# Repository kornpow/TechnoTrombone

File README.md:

# TechnoTrombone
Trombone Tutor for Raspberry Pi, and using Adafruit Neopixels

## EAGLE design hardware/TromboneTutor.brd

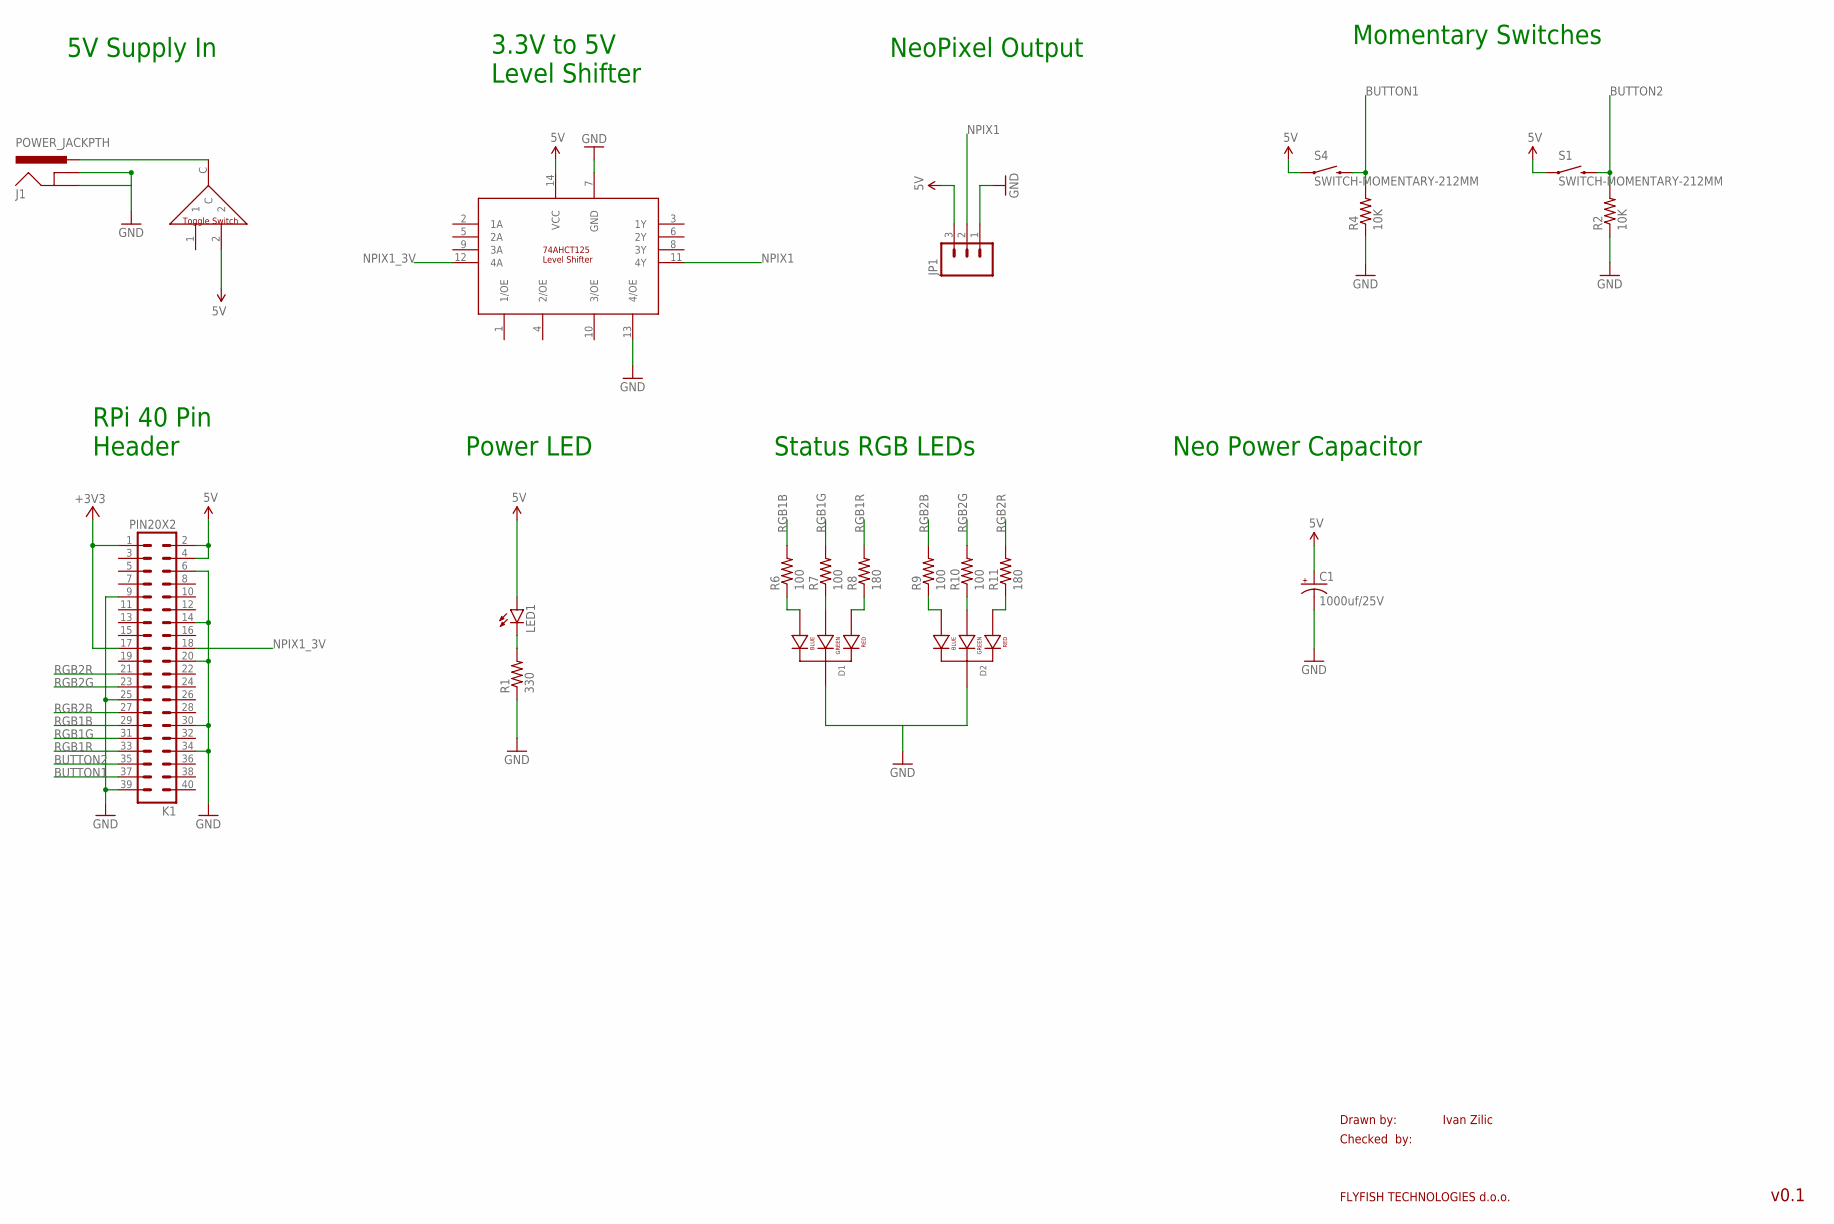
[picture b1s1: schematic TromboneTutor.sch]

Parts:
C1: 1000uf/25V; CPOL-RADIAL-1000UF-25V-KIT
D1, D2: LED-RGB-CC-THRUDIFFUSE; LED-RGB-THRU
J1: POWER_JACKPTH; POWER_JACK_PTH
JP1: M03PTH; 1X03
K1: PIN20X2; PIN_20X2
LED1: LED5MM
R1: 330; AXIAL-0.3
R2, R4: 10K; AXIAL-0.3-KIT
R6, R7, R9, R10: 100; AXIAL-0.3
R8, R11: 180; AXIAL-0.3
S1, S4: SWITCH-MOMENTARY-212MM; TACTILE-PTH-12MM
U$1: 74AHCT125_LEVELSHIFT; DIL14
U$2: TOGGLE_SWITCH_ESTORE

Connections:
5V: C1.+, JP1.3, K1.2, K1.4, LED1.A, S1.1, S4.1, U$1.14 (VCC), U$2.2
+3V3: K1.1, K1.17
BUTTON1: K1.37, R4.P$2 (2), S4.3 (2)
BUTTON2: K1.35, R2.P$2 (2), S1.3 (2)
GND: C1.-, D1.2 (CATHODE), D2.2 (CATHODE), J1.GND, J1.GNDBREAK, JP1.1, K1.6, K1.9, K1.14, K1.20, K1.25, K1.30, K1.34, K1.39, R1.P$1 (1), R2.P$1 (1), R4.P$1 (1), U$1.7 (GND), U$1.13 (4/OE)
unnamed: J1.PWR, U$2.C
unnamed: D1.4 (BLUE_CATHODE), R6.P$1 (1)
unnamed: D1.3 (GREEN_CATHODE), R7.P$1 (1)
unnamed: D1.1 (RED_CATHODE), R8.P$1 (1)
unnamed: D2.4 (BLUE_CATHODE), R9.P$1 (1)
unnamed: LED1.K (C), R1.P$2 (2)
unnamed: D2.3 (GREEN_CATHODE), R10.P$1 (1)
unnamed: D2.1 (RED_CATHODE), R11.P$1 (1)
NPIX1: JP1.2, U$1.11 (4Y)
NPIX1_3V: K1.18, U$1.12 (4A)
RGB1B: K1.29, R6.P$2 (2)
RGB1G: K1.31, R7.P$2 (2)
RGB1R: K1.33, R8.P$2 (2)
RGB2B: K1.27, R9.P$2 (2)
RGB2G: K1.23, R10.P$2 (2)
RGB2R: K1.21, R11.P$2 (2)

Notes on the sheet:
Drawn by:
Checked by:
FLYFISH TECHNOLOGIES d.o.o.
Ivan Zilic
v0.1
NeoPixel Output
3.3V to 5V Level Shifter
RPi 40 Pin Header
5V Supply In
Power LED
Status RGB LEDs
Momentary Switches
Neo Power Capacitor

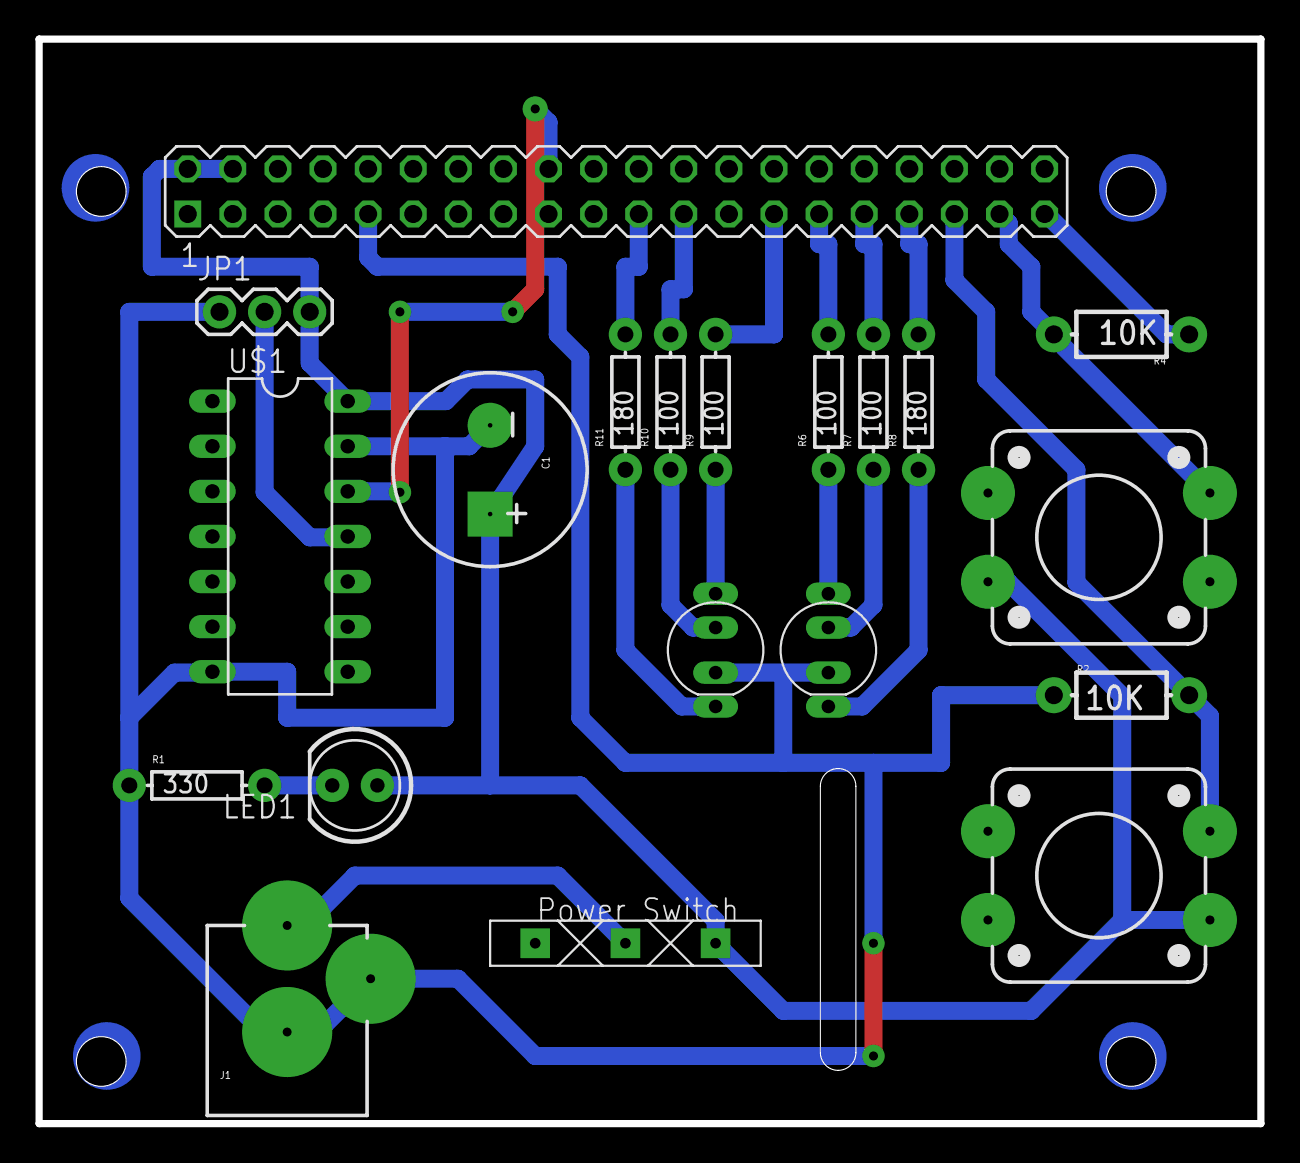
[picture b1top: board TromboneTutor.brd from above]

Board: 2 copper layers, 68.8 x 61.1 mm, 20 parts (0 on the bottom side), 21 nets.

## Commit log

2015-04-23 Added files to show changes to RPi
2015-04-23 Added the emailme script
2015-04-24 Code for basic LED control, and Button interrupts
2015-04-24 Embedded the Neopixel library into the project
2015-04-24 Updated Rpi Changelog
2015-04-29 PD Data mixed with Lights
2015-04-29 Puredata string and connection with python using patchbay
2015-05-05 Added the Eagle Files
2015-05-06 TechnoTrombone Final Code

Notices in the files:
parts and their libraries:
SparkFun-LED: Licensing: Creative Commons ShareAlike 4.0 International - https://creativecommons.org/licenses/by-sa/4.0
